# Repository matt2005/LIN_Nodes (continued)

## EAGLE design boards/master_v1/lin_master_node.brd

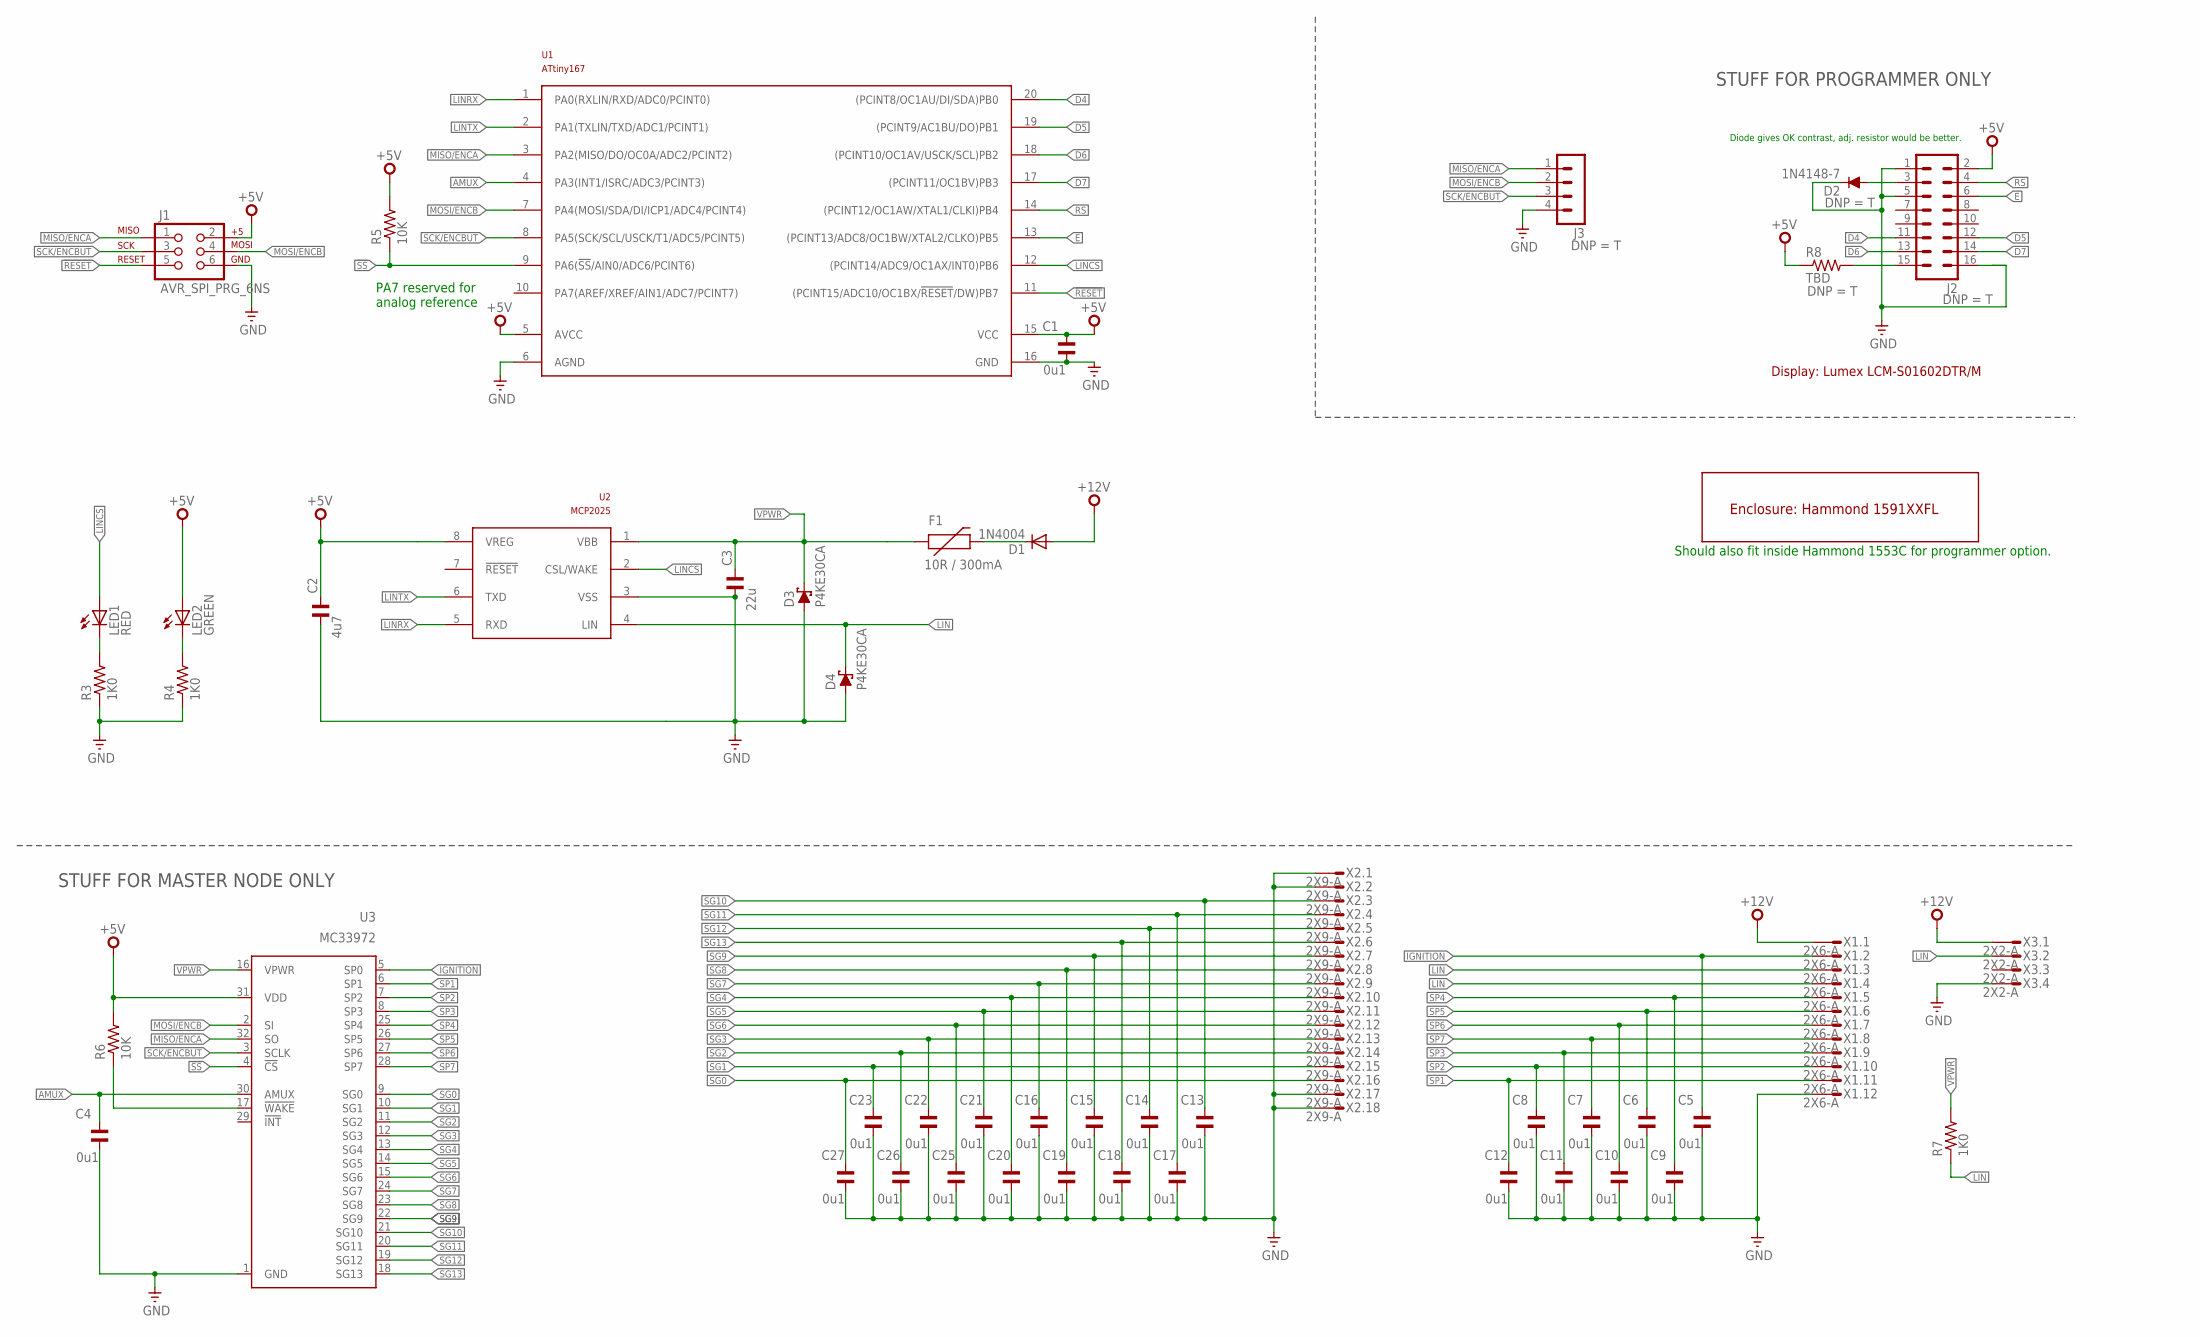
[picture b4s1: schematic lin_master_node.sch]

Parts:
C1, C4: 0u1; C050-024X044; PARTNO FK28X7R1H104K
C2: 4u7; C050-024X044; PARTNO FK28X5R0J475K
C3: 22u; C050-024X044; PARTNO FK22X5R1E226M
C5, C6, C7, C8, C9, C10, C11, C12, C13, C14, C15, C16, C17, C18, C19, C20, C21, C22, C23, C25, C26, C27: 0u1; C0603K; PARTNO C1608X7R1H104M080AA
D1: 1N4004; DO41-10; PARTNO 1N4004-TP
D2: 1N4148-7; DO35-7; PARTNO 1N4148TA
D3, D4: P4KE30CA; DO41-10; PARTNO P4KE30CA
F1: 10R / 300mA; PTC; PARTNO CMF-RL10-0
J1: AVR_SPI_PRG_6NS; 2X3-NS
J2: MA08-2
J3: MA04-1
LED1: RED; LED3MM; PARTNO C4SMF-RJS-CT0W0BB2
LED2: GREEN; LED3MM; PARTNO C4SMF-GJS-CV0Y0792
R3, R4, R7: 1K0; 0207/10; PARTNO CF14JT1K00
R5, R6: 10K; 0207/10; PARTNO CF14JT10K0
R8: TBD; 0207/10
U1: ATtiny167; SO20W; PARTNO ATTINY167-SU
U2: MCP2025; SO08; PARTNO MCP2025-500E/SN
U3: MC33972; SOIC32W; PARTNO MC33972ATEW
U$1: 1591XXAFL; PARTNO 1591XXAFLBK
X1: 2X6-A; 4-794618-2; PARTNO 4-794618-2
X2: 2X9-A; 4-794618-8; PARTNO 4-794618-8
X3: 2X2-A; 3-794618-4; PARTNO 3-794618-4

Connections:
!RESET: J1.5, U1.11 ((PCINT15/ADC10/OC1BX/!RESET!/DW)PB7)
!SS: R5.1, U1.9 (PA6(!SS!/AIN0/ADC6/PCINT6)), U3.4 (!CS)
+5V: C1.1, C2.1, J1.2, J2.2, LED2.A, R5.2, R6.2, R8.1, U1.5 (AVCC), U1.15 (VCC), U2.8 (VREG), U3.31 (VDD)
+12V: D1.A, X1.1, X3.1
AMUX: C4.1, U1.4 (PA3(INT1/ISRC/ADC3/PCINT3)), U3.30 (AMUX)
D4: J2.11, U1.20 ((PCINT8/OC1AU/DI/SDA)PB0)
D5: J2.12, U1.19 ((PCINT9/AC1BU/DO)PB1)
D6: J2.13, U1.18 ((PCINT10/OC1AV/USCK/SCL)PB2)
D7: J2.14, U1.17 ((PCINT11/OC1BV)PB3)
E: J2.6, U1.13 ((PCINT13/ADC8/OC1BW/XTAL2/CLKO)PB5)
GND: C1.2, C2.2, C3.2, C4.2, C5.2, C6.2, C7.2, C8.2, C9.2, C10.2, C11.2, C12.2, C13.2, C14.2, C15.2, C16.2, C17.2, C18.2, C19.2, C20.2, C21.2, C22.2, C23.2, C25.2, C26.2, C27.2, D2.C, D3.A, D4.A, J1.6, J2.1, J2.5, J2.16, J3.4, R3.1, R4.1, U1.6 (AGND), U1.16 (GND), U2.3 (VSS), U3.1 (GND), X1.12, X2.1, X2.2, X2.17, X2.18, X3.4
IGNITION: C5.1, U3.5 (SP0), X1.2
LIN: D4.C, R7.1, U2.4 (LIN), X1.3, X1.4, X3.2
LINCS: LED1.A, U1.12 ((PCINT14/ADC9/OC1AX/INT0)PB6), U2.2 (CSL/WAKE)
LINRX: U1.1 (PA0(RXLIN/RXD/ADC0/PCINT0)), U2.5 (RXD)
LINTX: U1.2 (PA1(TXLIN/TXD/ADC1/PCINT1)), U2.6 (TXD)
MISO/ENCA: J1.1, J3.1, U1.3 (PA2(MISO/DO/OC0A/ADC2/PCINT2)), U3.32 (SO)
MOSI/ENCB: J1.4, J3.2, U1.7 (PA4(MOSI/SDA/DI/ICP1/ADC4/PCINT4)), U3.2 (SI)
unnamed: LED1.K (C), R3.2
unnamed: R6.1, U3.17 (!WAKE)
unnamed: LED2.K (C), R4.2
unnamed: D1.C, F1.P$2 (2)
unnamed: J2.15, R8.2
unnamed: D2.A, J2.3
RS: J2.4, U1.14 ((PCINT12/OC1AW/XTAL1/CLKI)PB4)
SCK/ENCBUT: J1.3, J3.3, U1.8 (PA5(SCK/SCL/USCK/T1/ADC5/PCINT5)), U3.3 (SCLK)
SG0: C27.1, U3.9 (SG0), X2.16
SG1: C23.1, U3.10 (SG1), X2.15
SG2: C26.1, U3.11 (SG2), X2.14
SG3: C22.1, U3.12 (SG3), X2.13
SG4: C20.1, U3.13 (SG4), X2.10
SG5: C21.1, U3.14 (SG5), X2.11
SG6: C25.1, U3.15 (SG6), X2.12
SG7: C16.1, U3.24 (SG7), X2.9
SG8: C19.1, U3.23 (SG8), X2.8
SG9: C15.1, U3.22 (SG9), X2.7
SG10: C13.1, U3.21 (SG10), X2.3
SG11: C17.1, U3.20 (SG11), X2.4
SG12: C14.1, U3.19 (SG12), X2.5
SG13: C18.1, U3.18 (SG13), X2.6
SP1: C12.1, U3.6 (SP1), X1.11
SP2: C8.1, U3.7 (SP2), X1.10
SP3: C11.1, U3.8 (SP3), X1.9
SP4: C9.1, U3.25 (SP4), X1.5
SP5: C6.1, U3.26 (SP5), X1.6
SP6: C10.1, U3.27 (SP6), X1.7
SP7: C7.1, U3.28 (SP7), X1.8
VPWR: C3.1, D3.C, F1.P$1 (1), R7.2, U2.1 (VBB), U3.16 (VPWR)

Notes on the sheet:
PA7 reserved for analog reference
Diode gives OK contrast, adj. resistor would be better.
Should also fit inside Hammond 1553C for programmer option.
STUFF FOR MASTER NODE ONLY
STUFF FOR PROGRAMMER ONLY
Display: Lumex LCM-S01602DTR/M

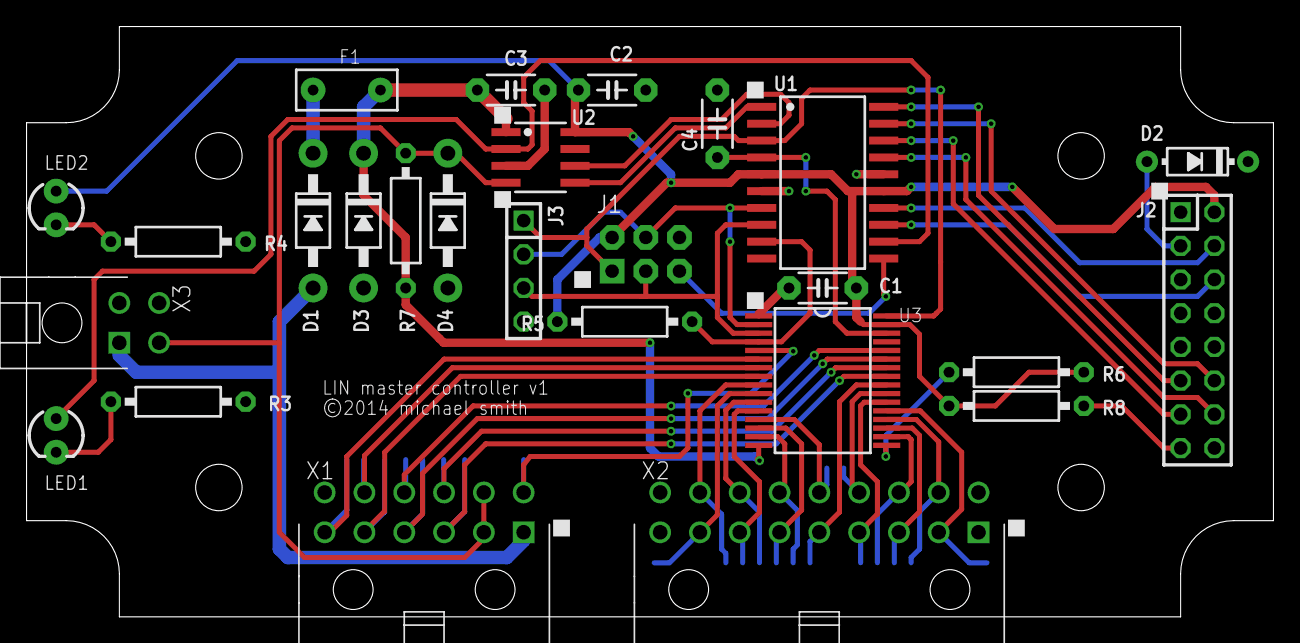
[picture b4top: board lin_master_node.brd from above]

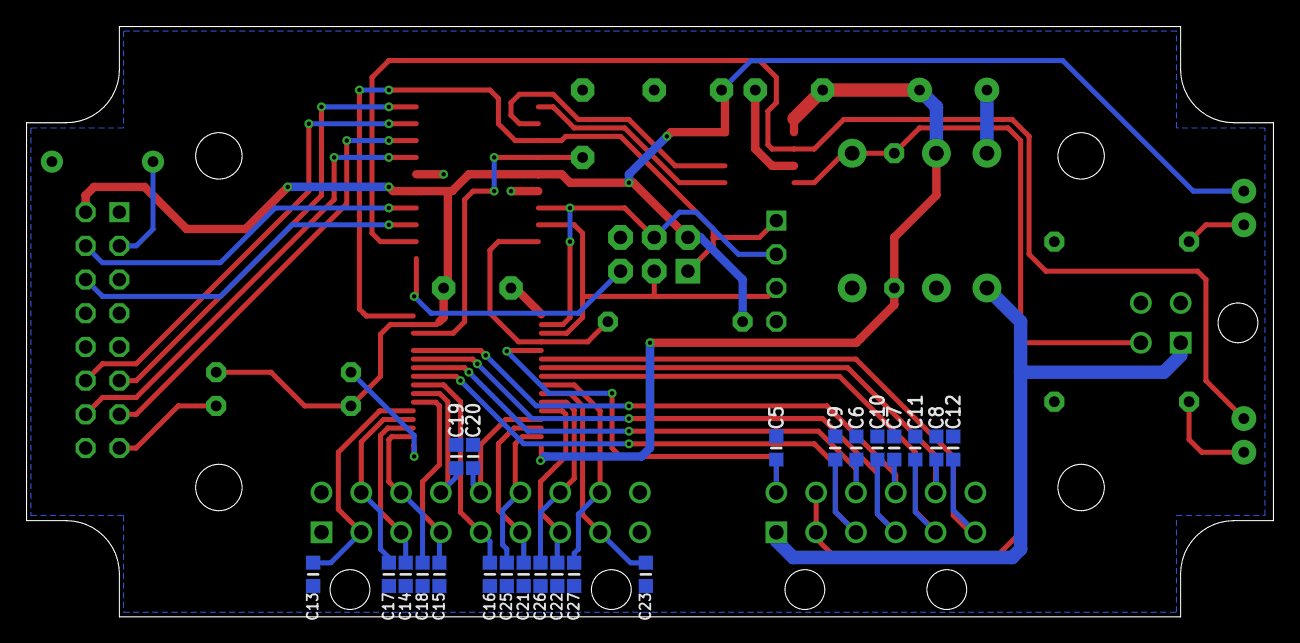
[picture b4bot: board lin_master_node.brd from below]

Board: 2 copper layers, 94.0 x 44.5 mm, 49 parts (22 on the bottom side), 48 nets.

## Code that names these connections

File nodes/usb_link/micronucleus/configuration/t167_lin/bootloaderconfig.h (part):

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 * 
 * Controller type: ATtiny 167 - 16 MHz with crystal
 * Configuration:   Standard configuration
 *       USB D- :   PB6
 *       USB D+ :   PB3
 *       Entry  :   Always
 *       LED    :   None
 *       OSCCAL :   No change due to external crystal
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 *                      external jumper. 
 *                      Adds 34 bytes.
 *
 *       JUMPER_PIN     Pin the jumper is connected to. (e.g. PB0)
 *       JUMPER_PORT    Port out register for the jumper (e.g. PORTB)  
 *       JUMPER_DDR     Port data direction register for the jumper (e.g. DDRB)  
 *       JUMPER_INP     Port inout register for the jumper (e.g. PINB)  
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
#define ENTRYMODE ENTRY_ALWAYS

#define JUMPER_PIN    PB0
#define JUMPER_PORT   PORTB 
#define JUMPER_DDR    DDRB 
#define JUMPER_INP    PINB 
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
#define LED_DDR     DDRA
#define LED_PORT    PORTA
#define LED_PIN     PA6

/*
 *  This is the implementation of the LED code. Change the configuration above unless you want to 
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
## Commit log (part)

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2014-05-01 Refactor LIN slave into separate device + slave modules
2014-05-01 Add a wrapper around the MC33972 driver that understands switch assignments
2014-05-01 Adjust relay/switch assignments
2014-05-02 Hardcode ignition input on SP0
2014-05-02 Move all pin init to the board module
2014-05-02 redundant comment
2014-05-02 Minor Serial tweaks
2014-05-03 Make Timer usefully subclassable
2014-05-03 Correct type for the master relay frame
2014-05-03 Cheaper one-shot decrementer for up to 60s
2014-05-05 More switch types
2014-05-05 WIP refactoring menu
2014-05-05 MC33972 class -> namespace
2014-05-05 Menu class -> namespace
2014-05-06 fix board define check for master node
2014-05-06 refactor the MC33972 code for more smaller
2014-05-06 Move pin config back out into drivers, centralising seems not to work
2014-05-06 Split out relay logic from top-level code
2014-05-06 Add a changed flag to the MC33972 driver
2014-05-07 Standalone programmer app
2014-05-07 Add a common 'display' class with move and clear methods
2014-05-07 hd44780 driver inherits from Display
2014-05-07 Sketch in the menus for the programmer
2014-05-09 Rotary encoder for the programmer
2014-05-10 Implement a simpler form of the programmer protocol
2014-05-10 Cleanliness
2014-05-10 Implement node discovery, merge 'explore' and 'setup'
2014-05-10 Fix master handling of ConfigRequest headers
2014-05-10 Fix timeouts for network exploration
2014-05-10 Add a string table lookup function
2014-05-10 use string table lookup
2014-05-10 Implement editing for master parameters
2014-05-10 Parameter editing for the power node.
2014-05-11 Start the slave sleep timer at power-on, not just after receiving a header.
2014-05-11 Don't erase the EEPROM when flashing
2014-05-11 Teach the programmer to disappear off the bus
2014-05-12 Fix power slave handling of relay frame
2014-05-12 fix programmer relay assignment table
2014-05-12 un-break switch debounce
2014-05-12 debug prettiness
2014-05-13 bump the retry timer back up to 100ms for safety's sake
2014-05-13 turn off LINCS as a visual indication when the master is 'asleep'
2014-05-13 New bit array class
2014-05-13 Be smarter about finding things to build
2014-05-13 missed pathway lighting case
2014-05-13 Use edit mode to render parameters in master setup mode
2014-05-13 Use edit mode to draw parameters in relay setup mode
2014-05-14 doc tweaks
2014-05-17 Major tweak to the LCD driver to make it work with another display
2014-05-17 Sync programmer with protocol
2014-05-17 Tweak protocol def to make things work better
2014-05-29 Include guard
2014-06-05 Some example boards.
2014-06-05 boards/schematics for the dashboard and v3 power node
2014-06-11 Faster pixel output.
2014-06-11 New 64x32 panel
2014-06-11 More tuning the display output & frame time
    Adjust brightness values to get us a ~17ms frame time, no more
    flickering
    Tune the output loop to ~66µs, which seems to equate to ~7ms total
    transfer time per frame.
    Brightness looks OK at this level.
2014-06-12 Double-buffer display output, so that we can cleanly draw overlapping glyphs
2014-06-13 Shrink the light telltales to avoid crowding the speedo
2014-06-13 typo in previous commit
2014-06-13 Squeeze a few more bytes out
2014-06-13 Tinker with the text widget...
2014-06-14 Add a 'tenths' number glyph for voltage / tripmeter, consolidate the legend glyphs
2014-07-01 Refactor so that AVR node code and ARM dashboard code are proper peers
2014-07-01 Add reformat support to the nodes, run it once.
2014-07-01 Part number fixes
2014-07-04 Spin the power_v3 board, add more support code for it
2014-07-04 Unsigned math
2014-07-06 Tinkering with the programmer, start thinking about 20x4 display use
2014-07-07 more autogeneration, less typing
2014-07-07 Fix string table definitions so they don't eat all of RAM
2014-07-08 More autogen tinkering, getting better each time.
2014-07-08 cppcheck
2014-07-09 Fix node-present list initialisation
2014-07-09 Parameter editing for master node is working again
2014-07-14 (added file missed in previous commit)
2014-07-14 add hyphen to our character set
2014-07-14 Right-size some fields, remove a perf counter
2014-07-14 main loop perf counters don't make a lot of sense, don't handle interrupt time well
2014-07-15 Make sure the linker knows, no exceptions, no RTTI
2014-07-15 Less perf gunk in the dashboard codebase
2014-07-15 reformat pass
2014-07-15 Turn on LTO for minor space savings... investigate impact on stack usage
2014-07-16 Remove stale glyph prototypes
2014-07-16 Implement ReadByID error response
    Fixes #13 (was mostly already implemented)
2014-07-17 Reshuffle programmer edit mode definitions, add explore support for diagnostic mode
2014-07-17 more staticity
2014-07-17 Improve bus scan speed
2014-07-17 Work-in-progress for #32
2014-07-17 Move node protocol definitions out of the LIN namespace
    … since they aren’t LIN protocol definitions.
2014-07-17 Standards; use the U suffix on non-zero integer constants in some more places
2014-07-17 build fix
2014-07-18 Fixes for the LIN master task behaviour
    Aggressively reinit the LIN block before sending a new frame header.
    Rename methods to clarify master/slave task use.
    Avoid passing the current FID around as an argument, since it can be
    fetched from a register when needed.
2014-07-18 Wrong FID being used to select 1x vs. 2x LIN header transmission
2014-07-19 Fix pin assignments for the power_v3.1 board, verify LIN and SPI
    Fixes #10
2014-07-19 Fix off-by-one in parameter definition table
    Fixes #31
2014-07-19 Take a guess at the undocumented tENBL time; fixes a problem where the device ignores the first SPI write.
2014-07-19 Unconditionally return the board ID as parameter 0
    Fixes #40
2014-07-20 Disable the LIN_x_set_type macros; the 2x variant doesn't clear 1x mode.
2014-07-20 A very simple LIN dumper
    Connect the serial device to pin 1 on any AVR on the bus.
2014-07-20 Fix network-suspend when the programmer goes to info mode
2014-07-20 Code & data shrink for the programmer
2014-07-20 Implement error counter display for power nodes
    Fixes #14
2014-07-21 Integrate v-usb and become a simple USB device.
2014-07-23 Add polled-mode operation to the LIN slave
2014-07-23 Commandline tool, starting with one of the v-usb examples.
2014-07-24 more ignores
2014-07-26 Calibration for 16MHz
2014-07-26 Checkpoint USB tool - logging works.
2014-07-26 Licenses and project readme
2014-07-27 Update documentation for gendefs
2014-07-27 Add network-awake detection for the USB link
2014-07-27 Avoid hardcoding the master NAD
2014-07-27 Fix log buffering
2014-07-28 Tinkering with using an enhanced version of the LIN NCF file rather than our custom defs.
2014-07-28 Let's have a 'default' node with some generic parameters and a page attribute for parameters in general
2014-07-29 More tinkering with the NCF parser. Looking like maybe it can be useful.
2014-08-04 I just can't stay away...
2014-08-04 Master node builds. It got a bit big.
2014-08-04 Save a few more bytes with a temporary Parameter
2014-08-04 License goop
2014-08-05 Convert the V3 power node to the new world
2014-08-08 Work in progress bringing the tester/programmer into the new world
2014-08-15 Make the standalone programmer compile in the new world
2014-08-17 Fix reset vector patching logic
2014-08-17 Checkpoint: USB link becoming a master
2014-08-17 Optimise encoding valid ranges (mostly for reading purposes)
    Also disable the programmer build… it’s way too big right now and needs
    rethinking.
2014-08-17 Reduce complexity; bootloader installer can now generate its own uploadable
2014-08-17 Timestamp taken field doesn't need to be public
2014-08-17 Make sure we set the PCI field in MasterRequest/SlaveResponse responses
2014-08-18 Initialise response bytes to zero; this is less error-prone
2014-08-18 USB tool can be a master, pushes normal master off the bus
    This is so that there’s a master when we’re flashing the master…
2014-08-18 Add parameter existence check function.
2014-08-18 Beat on the tool until it can read parameters.
    Add timestamps to log messages.
    Wait for the bus to idle after claiming it.
2014-08-18 Maybe this time the commit for this file will stick?
2014-08-18 Catch up with formatting fixes
2014-08-24 Bootloader debug parameters
2014-08-28 Firmware iterator-like thing
2014-08-30 Dump parameters to file, only print parameters the node gave us. Smarter list of node addresses to scan.
2014-08-31 Switch to JSON for the parameter file format; use this to make load/save much simpler.
2014-08-31 Implement firmware update (untested). Clean up argument parsing.
2014-09-01 checkpoint: bootloader flashing image & saving program info correctly.
2014-09-01 Better exception strings
2014-09-01 Improve the performance of send-only transactions like bulk transfers.
    Partially addresses #53
2014-09-01 Clear the EEPROM after update. Fixes #49
2014-09-26 Make link master-mode automatic as needed
2014-10-04 Report master protocol version from slave nodes
    This is the rel1 component of #59
2014-10-04 Build firmware bundle for power_v3
    After testing, fixes #61
2014-10-06 Better build rules for lintool
2014-10-16 Rename built products to match the lin_defs database
2014-10-16 Improve upload / readback behaviour
2014-10-16 Disable upload readback by default, fixes #64
2014-10-16 Print logs on successful exit
    Applicable to #66 but does not appear to fix it.
2014-10-16 <param.h> documentation.
2014-10-16 EEPROM clear doesn't/can't work like this
    Filed #69 to track fixing this properly
2014-10-18 Reformat, documentation
2014-10-31 Updated directory descriptions
2014-10-31 Node parameter init will reset parameters after refresh
    Fixes #69
2014-11-01 Deprecate the power_v1 firmware
    Fixes #73
2014-11-20 Teach static bitarrays how to compare with each other
2014-11-21 Less spew, more documentation
2014-11-21 Fix #78 by correcting the size of the Board::kConfigMagic write
    Replace some magic numbers with constants from lin_defs, and add API to
    Board to check for forced bootloader entry.
    Remove stale PowerV1 references.
    Entangled with some changes to PowerV3 status reporting related to #77.
2014-12-13 Fix formatting of non-request frames
2014-12-13 Increase master reboot timeout to avoid errors leaving bootloader mode
2014-12-14 Fix load/save parameter filename arg indexes
2014-12-14 Switch from Jzon to SuperSimpleJSON, load/save is working now
    Note that this does not produce pretty-printed JSON, and the parser
    chokes on pretty-printed JSON making life hard for anyone that wants to
    edit the save files, but it serves the immediate purpose of parameter
    save/restore around firmware updates.
    Fixes #62
2014-12-14 Fix switch encoding parameter indexing when converting switch inputs to assignments,
    Fixes #80
2014-12-14 make status address readout cleaner
2014-12-14 Add option to preserve node configuration across firmware update
    Fixes #85
2014-12-14 Print parameter values as both decimal and hex
2014-12-15 Better info message when skipping nodes during firmware update
2014-12-16 Note why it's OK for LightsDown to be de-asserted when markers are on.
    Fixes #88
2014-12-17 Add a safe accessor for values updated in interrupt context.
2014-12-18 Cut the 'stay awake' timer down to 20 seconds.
    This is mostly for testing purposes, as waiting 50 seconds for the
    system to sleep is tedious. Need to determine what the final
    ‘production’ value should be.
2014-12-18 Initialise saturating counters to zero
    Fixes #91
2014-12-18 Add range checking to bitarray.
    This could probably be smarter, but for now Fixes #79
2014-12-20 Don't disable the watchdog in the bootloader installer
2014-12-20 Fuse the watchdog permanently on
2014-12-20 Remove freemem panic, not really useful right now
2014-12-20 Remove leftover debug output
2014-12-21 Adjust constants for turn signal and wiper times to match NCF definitions
    Fixes #98
2014-12-21 Changes suggested by cppcheck
